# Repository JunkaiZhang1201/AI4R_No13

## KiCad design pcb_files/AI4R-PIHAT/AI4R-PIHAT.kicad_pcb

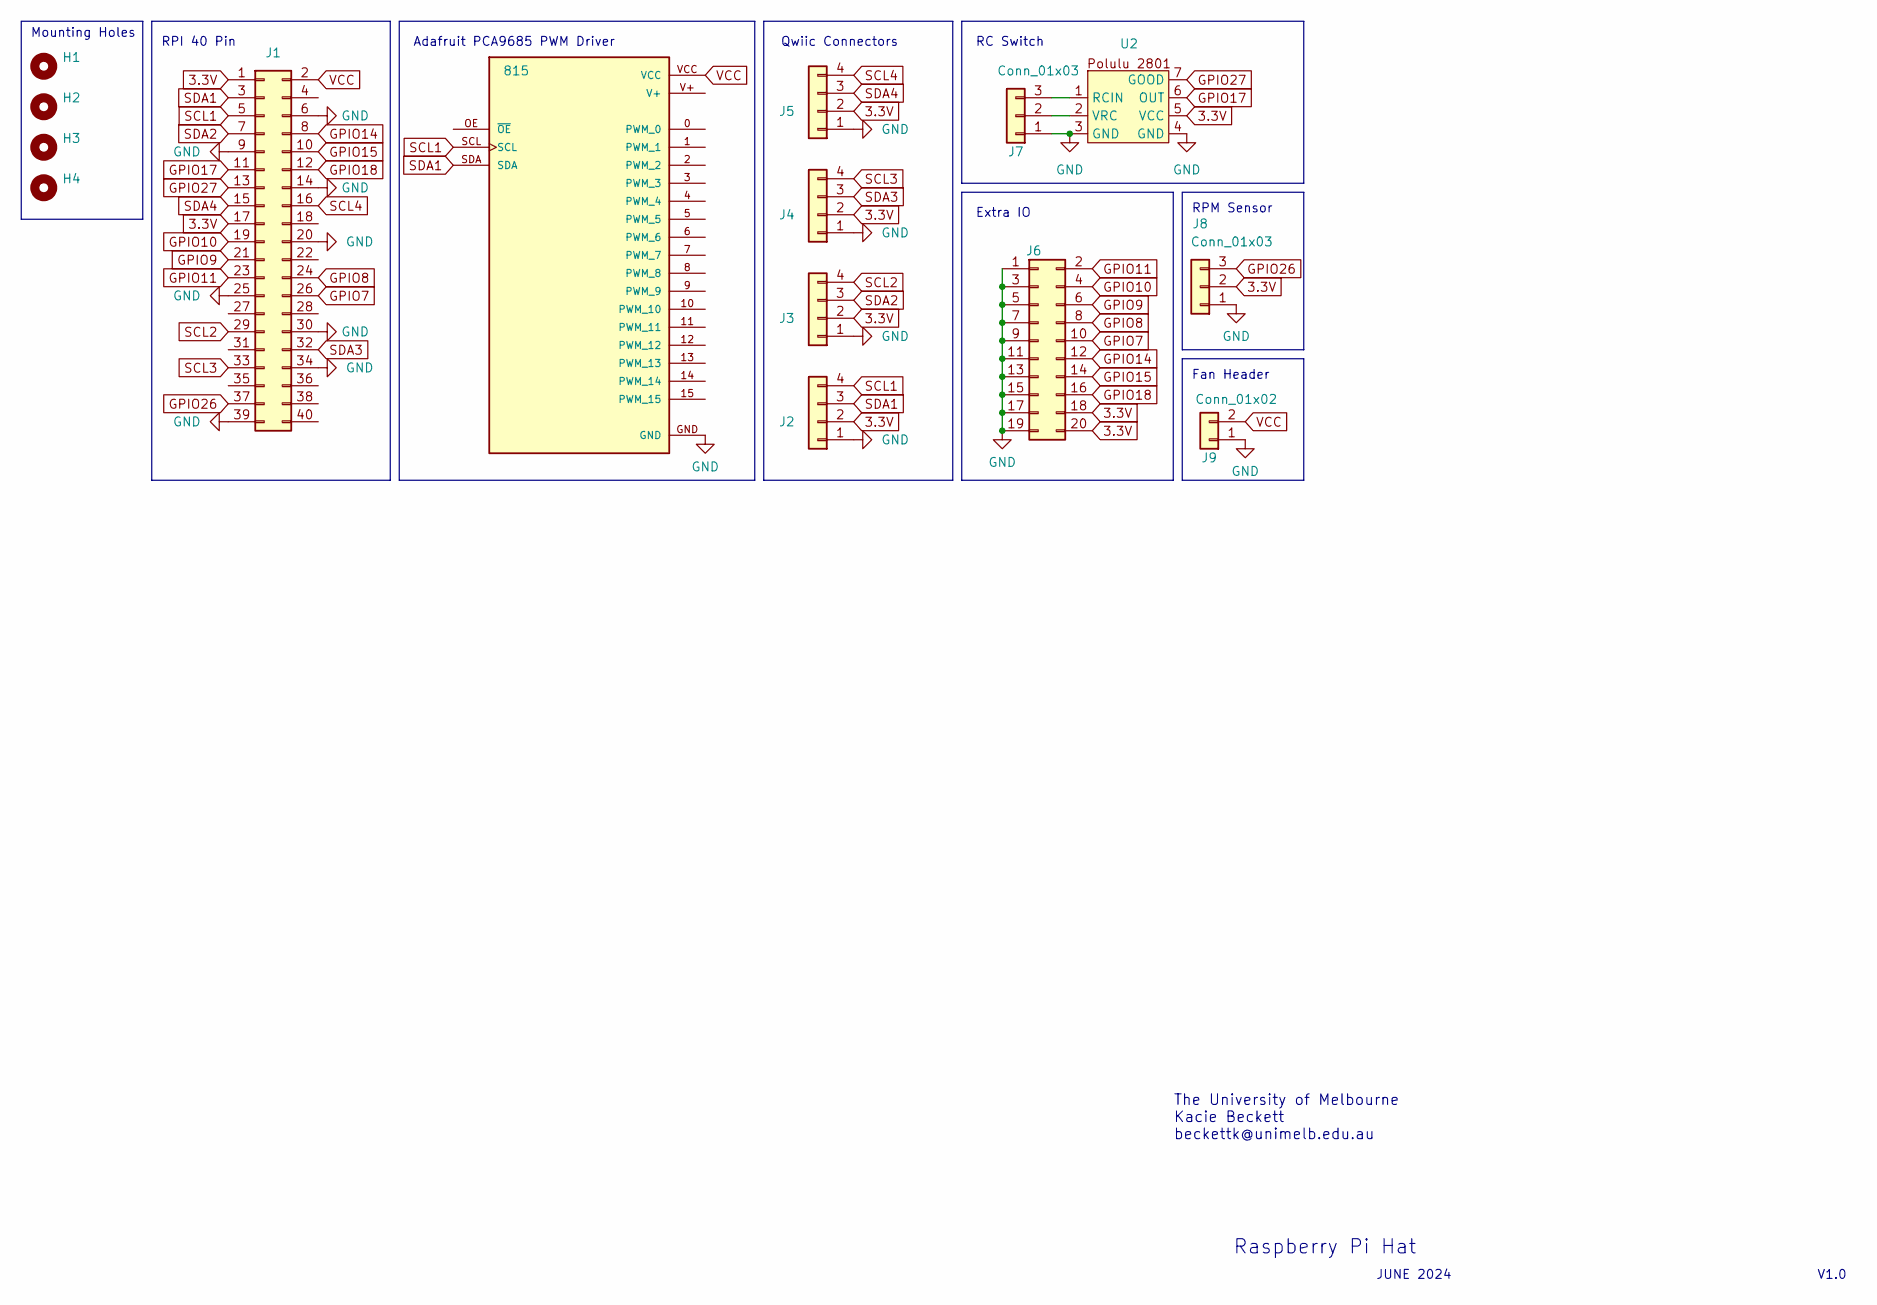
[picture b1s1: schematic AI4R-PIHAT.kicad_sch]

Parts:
H1, H2, H3, H4: MountingHole; MountingHole_2.7mm_M2.5_Pad
J1: Conn_02x20_Odd_Even; PinHeader_2x20_P2.54mm_Vertical
J2, J3, J4, J5: Conn_01x04; JST_SH_SM04B-SRSS-TB_1x04-1MP_P1.00mm_Horizontal
J6: Conn_02x10_Odd_Even; PinHeader_2x10_P2.54mm_Vertical
J7, J8: Conn_01x03; PinHeader_1x03_P2.54mm_Vertical
J9: Conn_01x02; PinHeader_1x02_P2.54mm_Vertical
U1: 815; Polulu-PCA9685; PARTREV C
U2: 2801RCSwitch

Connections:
3.3V: J1.1, J1.17, J2.2, J3.2, J4.2, J5.2, J6.18, J6.20, J8.2, U2.5 (VCC)
GND: J1.6, J1.9, J1.14, J1.20, J1.25, J1.30, J1.34, J1.39, J2.1, J3.1, J4.1, J5.1, J6.1, J6.3, J6.5, J6.7, J6.9, J6.11, J6.13, J6.15, J6.17, J6.19, J7.1, J8.1, J9.1, U1.GND, U2.3 (GND), U2.4 (GND)
GPIO7: J1.26, J6.10
GPIO8: J1.24, J6.8
GPIO9: J1.21, J6.6
GPIO10: J1.19, J6.4
GPIO11: J1.23, J6.2
GPIO14: J1.8, J6.12
GPIO15: J1.10, J6.14
GPIO17: J1.11, U2.6 (OUT)
GPIO18: J1.12, J6.16
GPIO26: J1.37, J8.3
GPIO27: J1.13, U2.7 (GOOD)
unnamed: J7.2, U2.2 (VRC)
unnamed: J7.3, U2.1 (RCIN)
SCL1: J1.5, J2.4, U1.SCL
SCL2: J1.29, J3.4
SCL3: J1.33, J4.4
SCL4: J1.16, J5.4
SDA1: J1.3, J2.3, U1.SDA
SDA2: J1.7, J3.3
SDA3: J1.32, J4.3
SDA4: J1.15, J5.3
VCC: J1.2, J9.2, U1.VCC

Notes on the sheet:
Extra IO
V1.0
Fan Header
Raspberry Pi Hat
Adafruit PCA9685 PWM Driver
RPI 40 Pin
RPM Sensor
RC Switch
JUNE 2024
Qwiic Connectors
The University of Melbourne Kacie Beckett beckettk@unimelb.edu.au
Mounting Holes

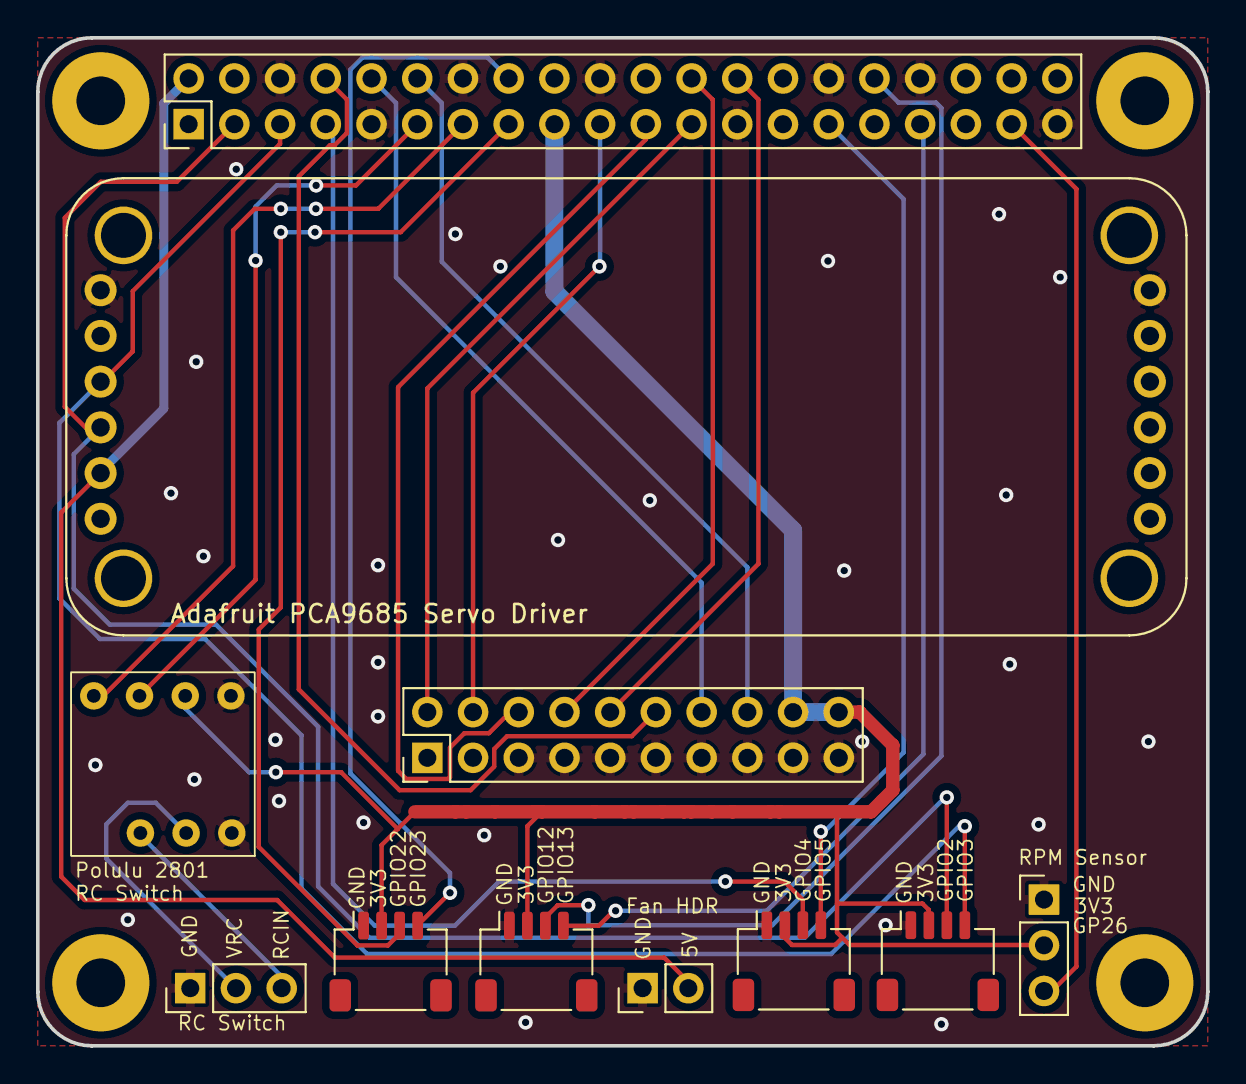
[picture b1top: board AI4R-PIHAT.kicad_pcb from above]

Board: 2 copper layers, 65.0 x 56.0 mm, 15 parts (0 on the bottom side), 24 nets.

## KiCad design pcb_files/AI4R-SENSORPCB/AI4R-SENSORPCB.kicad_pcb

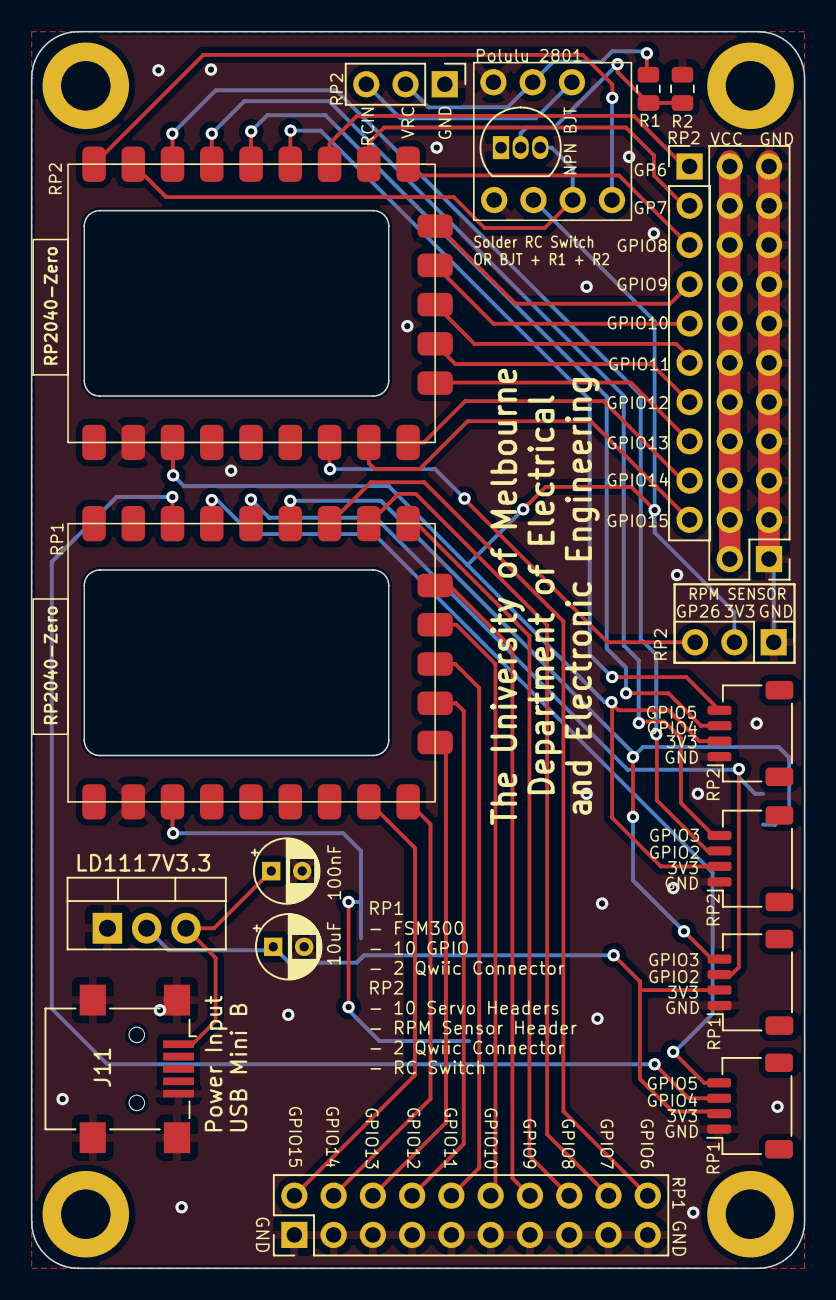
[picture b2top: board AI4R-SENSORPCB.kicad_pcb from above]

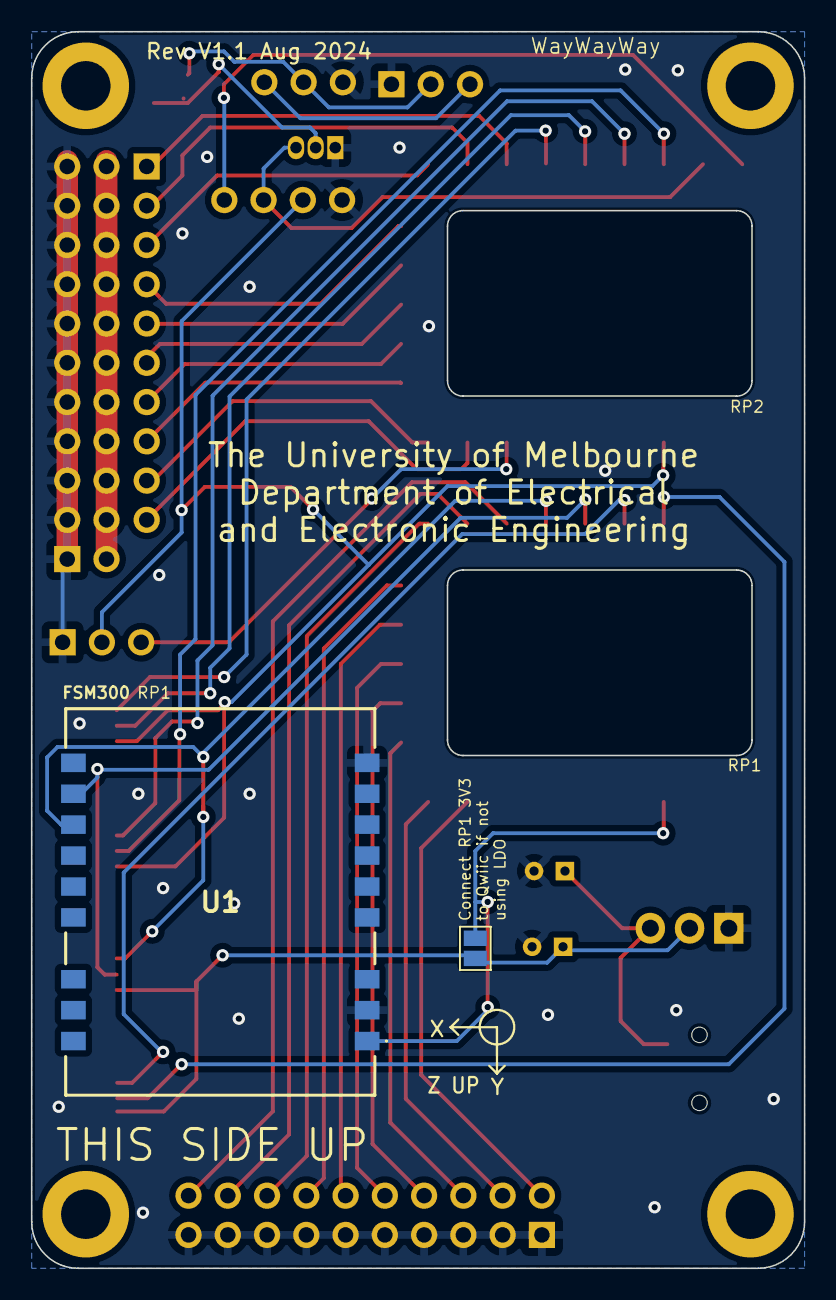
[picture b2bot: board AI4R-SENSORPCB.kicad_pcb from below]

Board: 2 copper layers, 50.0 x 80.0 mm, 25 parts (2 on the bottom side), 40 nets.

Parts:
C1: 10uF; CP_Radial_D4.0mm_P2.00mm
C2: 100nF; CP_Radial_D4.0mm_P2.00mm
H1, H2, H3, H4: MountingHole; MountingHole_3.2mm_M3_DIN965_Pad
J2, J3, J4, J5: Conn_01x04; JST_SH_SM04B-SRSS-TB_1x04-1MP_P1.00mm_Horizontal
J6: Conn_02x11_Odd_Even; PinHeader_2x11_P2.54mm_Vertical
J7, J9: Conn_01x03; PinHeader_1x03_P2.54mm_Vertical
J8: Conn_01x10; PinHeader_1x10_P2.54mm_Vertical
J10: Conn_02x10_Odd_Even; PinHeader_2x10_P2.54mm_Vertical
J11: USB_B_Mini; USB_Mini-B_Lumberg_2486_01_Horizontal
JP1: SolderJumper_2_Open; SolderJumper-2_P1.3mm_Open_Pad1.0x1.5mm
Q1: 2N3904; TO-92_Inline
R1, R2: R; R_0805_2012Metric
RP1, RP2: RP2040-Zero
U1: FSM300
U2: 2801RCSwitch
U3: LD1117V3.3; TO-220-3_Vertical

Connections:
3V3: JP1.1 (A), RP1.21 (3V3), U1.1 (VDD)
3V3B: J4.2, J5.2, J9.2, RP2.21 (3V3), U2.5 (VCC)
3V3PS: C1.1, J2.2, J3.2, JP1.2 (B), U3.2 (VO)
GND: C1.2, C2.2, J2.1, J3.1, J4.1, J5.1, J6.1, J6.3, J6.5, J6.7, J6.9, J6.11, J6.13, J6.15, J6.17, J6.19, J6.21, J7.1, J9.1, J10.1, J10.3, J10.5, J10.7, J10.9, J10.11, J10.13, J10.15, J10.17, J10.19, J11.5 (GND), J11.6 (Shield), Q1.1 (E), R2.1, RP1.22 (GND), RP2.22 (GND), U1.2 (GND_1), U1.9 (PS0/WAKEN), U2.3 (GND), U2.4 (GND), U3.1 (GND)
GP6: J10.20, RP1.7 (GP6)
GP6B: J8.1, RP2.7 (GP6)
GP7: J10.18, RP1.8 (GP7)
GP7B: J8.2, RP2.8 (GP7)
GP8: J10.16, RP1.9 (GP8)
GP8B: J8.3, RP2.9 (GP8)
GP9: J10.14, RP1.10 (GP9)
GP9B: J8.4, RP2.10 (GP9)
GP10: J10.12, RP1.11 (GP10)
GP10B: J8.5, RP2.11 (GP10)
GP11: J10.10, RP1.12 (GP11)
GP11B: J8.6, RP2.12 (GP11)
GP12: J10.8, RP1.13 (GP12)
GP12B: J8.7, RP2.13 (GP12)
GP13: J10.6, RP1.14 (GP13)
GP13B: J8.8, RP2.14 (GP13)
GP14: J10.4, RP1.15 (GP14)
GP14B: J8.9, RP2.15 (GP14)
GP15: J10.2, RP1.16 (GP15)
GP15B: J8.10, RP2.16 (GP15)
GP26B: J9.3, RP2.17 (GP26)
GPIO1B: RP2.1 (GP0), U2.7 (GOOD)
GPIO2B: Q1.3 (C), RP2.2 (GP1), U2.6 (OUT)
unnamed: J7.2, R1.1, U2.2 (VRC)
unnamed: J7.3, U2.1 (RCIN)
unnamed: Q1.2 (B), R1.2, R2.2
SCL1: J2.4, RP1.6 (GP5), U1.12 (SCL/SCK/RXD)
SCL2: J3.4, RP1.4 (GP3)
SCL3: J4.4, RP2.6 (GP5)
SCL4: J5.4, RP2.4 (GP3)
SDA1: J2.3, RP1.5 (GP4), U1.11 (SDA/MISO/TXD)
SDA2: J3.3, RP1.3 (GP2)
SDA3: J4.3, RP2.5 (GP4)
SDA4: J5.3, RP2.3 (GP2)
VCC: J6.2, J6.4, J6.6, J6.8, J6.10, J6.12, J6.14, J6.16, J6.18, J6.20, J6.22
VCC_TOF: C2.1, J11.1 (VBUS), U3.3 (VI)

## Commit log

2023-07-16 Created package with minimal C++ and Python nodes
2023-07-16 MIT License
2023-07-16 test push
2023-07-19 Brought the necessary drviers into the ROS2 workspace
2023-07-25 Minimal OOP Python and C++ node examples
2023-07-25 Nodes can run successfully now
2023-07-25 OOP Python pub and sub node examples
2023-07-26 cpp OOP pub and sub examples
2023-07-27 Working ServoPulseWidth.msg C++ subscriber
2023-07-29 multiple_pub_sub_cpp_node.cpp example to sub and pub to multiple nodes
2023-07-31 Looping C++ node with frequency
2023-08-01 Initial pwm_driver_node succesfully built
2023-08-01 Fixed ServoPulseWidth.channel data type and changed the i2c device number
2023-08-02 changed i2c number to test ssh push and pull
2023-08-08 timer callback test and traxxas node started
2023-08-08 gitignore build, install and logs folder
2023-08-08 corrected gitignore
2023-08-08 removed build install log
2023-08-08 Revert "removed build install log"
    This reverts commit 39c37bde36dd7d1272e7300ee1219982d8653434.
2023-08-08 Fully implemented Bill and Micah's capabilities
2023-08-08 Generated custom msg EscAndSteering
2023-08-09 All subscribers except for object_detected implemented
2023-08-09 Basic FSM: Directly Enable and Disable Traxxas
2023-08-09 FSM with commands timeout and safety check before enabling
2023-08-11 code_on_pi
2023-08-11 intial keyboard_teleop with bugs
2023-08-11 Revert "intial keyboard_teleop with bugs"
    This reverts commit 7cedc9a4b5387ef3652117e10af01ce80bbe9e83
2023-08-15 Deleted build, install, log folders
2023-08-15 policy_node.py
2023-08-15 temp change to git ignore
2023-08-15 temp adding back build install log
2023-08-15 another attempt at removing build install log
2023-08-15 added back the install log build folders to the git ignore file
2023-08-15 Merged CV
2023-08-15 custom messages for CV
2023-08-15 Fixed bugs preventing running of policy_node.py
2023-09-11 Added web interface for the ai4r nodes used to drive traxxas cars
2023-09-11 Minor correction to the default line detector config file to make Hue cover the full range of colour
2023-09-12 Update 4 files
    - /ros2_ws/src/ai4r_pkg/src/traxxas_node.cpp
    - /ros2_ws/src/ai4r_pkg/include/ai4r_pkg/traxxas_node.hpp
    - /web_interface/html/js/rosbridge_for_ai4r.js
    - /web_interface/html/ai4r_tab_workflow.html
2023-09-12 Minor corrections to change ImageProcessor name to Line Detector
2023-09-12 Changed files name of ImageProcessor to line_detector_node
2023-09-12 added different max and min pulse width for sterring and esc
2023-09-12 corrected wrror
2023-09-12 correct type casting
2023-09-12 correct minor error
2023-09-12 corrected minor error
2023-09-12 actually correctd th error this time
2023-09-12 updated pw limits slightly
2023-09-12 remove debugging print line
2023-09-15 Added local copy of the roslib.min.js so that the web interface can be run without an internet connection
2023-09-15 Updated web interface for send commands direct to the traxxas node
2023-09-16 Updated default command values in the traxxas node web interface command boxes to be 20 instead of 100
2023-09-16 Updated the traxxas web interface default commands to be safer values (20 instead of 100)
2024-03-01 Dummy git test
2024-03-01 Simple mux test with bugs to fix
2024-03-03 mux scripts first draft done, required prelim testing
2024-03-06 Mux test: Refactored code, used more meaningful names
2024-03-06 Attempt at troubleshooting I2C connection of RPi to PCA9685
2024-03-09 Swapped steering and esc channels
2024-03-13 Run shell scripts with sudo
2024-03-13 Change servo port to x42
2024-03-27 Removed topic_names.hpp
2024-05-03 New directory for docker files
2024-05-03 Upload New File
2024-05-13 Minimal working example publishing video cam images to /image topic
2024-05-17 Image resize before publishing
2024-06-06 Added stream_oak.py for RPi camera test, Changed QoS for image publishing to qos_profile_sensor_data
2024-06-07 Added OAK-D streaming publisher node
2024-06-11 Added simple C/C++ gpiod code for getting value of a line
2024-06-11 gpiod_ctxless edit
2024-06-11 Wrapped gpio rc switch in ros2 - does not compile
2024-06-11 Commit for Phu to debug
2024-06-27 Moved gpiod_rc_switch_testing.cpp out to ai4r-system folder -> Compiles successfully with g++-11 and modified tasks.json
2024-06-27 Minimal working gpiod example: gpid_chip_close and gpiod_line_release commented out because it triggers a segmentation fault
2024-06-27 renamed non-ros (just c++) gpiod testing code
2024-06-27 Minimal ROS2 gpiod working
2024-06-29 5Hz gpio polling
2024-07-02 Added custom foxglove_bridge_launch.xml to ai4r_pkg
2024-07-02 gpiod_rc_switch_testing.cpp publishes 'GOOD' & 'OUT' signals, esc_calibration_service_testing.cpp with full esc calibration untested
2024-07-09 Adjusted ESC pulse width values to eliminate high-pitched noise on car #1
2024-07-09 Custom QoS profile for streaming OAK-D camera feed
2024-07-24 Duplicated copy of old traxxas node
2024-07-26 Made Traxxas node run without PCA servo board for dev purposes
2024-08-02 Traxxas node complete: Successfully tested on personal laptop using Foxglove
2024-08-04 add pcb project files
2024-08-04 clean pcb files
2024-08-07 Launch traxxas_node_params.yaml from traxxas_launch.py
2024-08-09 Uncommented PCA___ servo driver code in traxxas_node.cpp
2024-08-09 Fixed /request topic msg type issue
2024-08-09 New AI4R Foxglove UI json
2024-08-09 Renamed 'request' topic to 'traxxas_request' to avoid name clash with Foxglove 'request'
2024-08-09 Removed namespacing of traxxas node in launch file for now
2024-08-09 Updated Foxglove UI json
2024-08-09 Changed camera resolution from 1080p to 800p
2024-08-14 New stream oak code with constants to change capture fps and streaming fps
2024-08-14 Toggle camera stream added
2024-08-16 Changed cam resolution to 800p. Commented out publish of autonomous mode when remote switch is flipped to autonomous mode
2024-08-19 fix gerber errors
2024-08-19 remove pcb lock
2024-08-23 Launch files and ConePointsArray msg
2024-08-25 add parser for the sensor pcb to publish sensor data topics
2024-08-25 add mcu code workspace for the sensor pcb
2024-08-26 update documentation
2024-08-26 update sensor messages
2024-08-26 add multithreading for sensor pcb to double output speed
2024-08-27 Cone detection wrapped in ROS
2024-08-27 Foxglove UI additions
2024-08-27 Added IR Dot projection
2024-08-27 Absolute blob file path for RPi
2024-08-27 UI changes to display cone locations
2024-08-27 Update camera height, camera stretch properties, FPS, SDN settings for real-time
2024-08-28 Updated blob file and path
2024-08-28 Removed TODO and made camera fps a global variable
2024-08-28 Corrected rc switch pins to match pcb
2024-08-28 Revert accidental removal of self.pipeline
2024-08-28 Global variable parameters for cone detector settings
2024-08-28 stream detection
2024-08-28 Add TODO - Publish frame to ROS
2024-08-28 Revert Threads
